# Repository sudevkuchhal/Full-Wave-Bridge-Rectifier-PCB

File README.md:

# Full Wave Bridge Rectifier PCB

## Overview
Designed and fabricated a Full Wave Bridge Rectifier PCB using KiCad.  
The circuit converts AC input into stable DC output using a diode bridge and filtering capacitor.

## Features
- Full wave AC to DC conversion
- Bridge rectifier using diodes
- Smoothing capacitor for ripple reduction
- LED power indicator

## Tools & Technologies
- KiCad (Schematic + PCB Design)
- PCB fabrication using etching method
- Soldering and hardware testing

## Learning Outcome
- PCB design workflow in KiCad
- Practical understanding of rectification
- Hands-on experience in circuit fabrication and testing
- Basics of power electronics implementation
## Project Images

### Final PCB

### Second PCB Image

### Soldering Process

### Etching Process

### Printed Layout / Setup

## Result
Successfully converted 12V AC input into stable DC output suitable for low-power electronic circuits.

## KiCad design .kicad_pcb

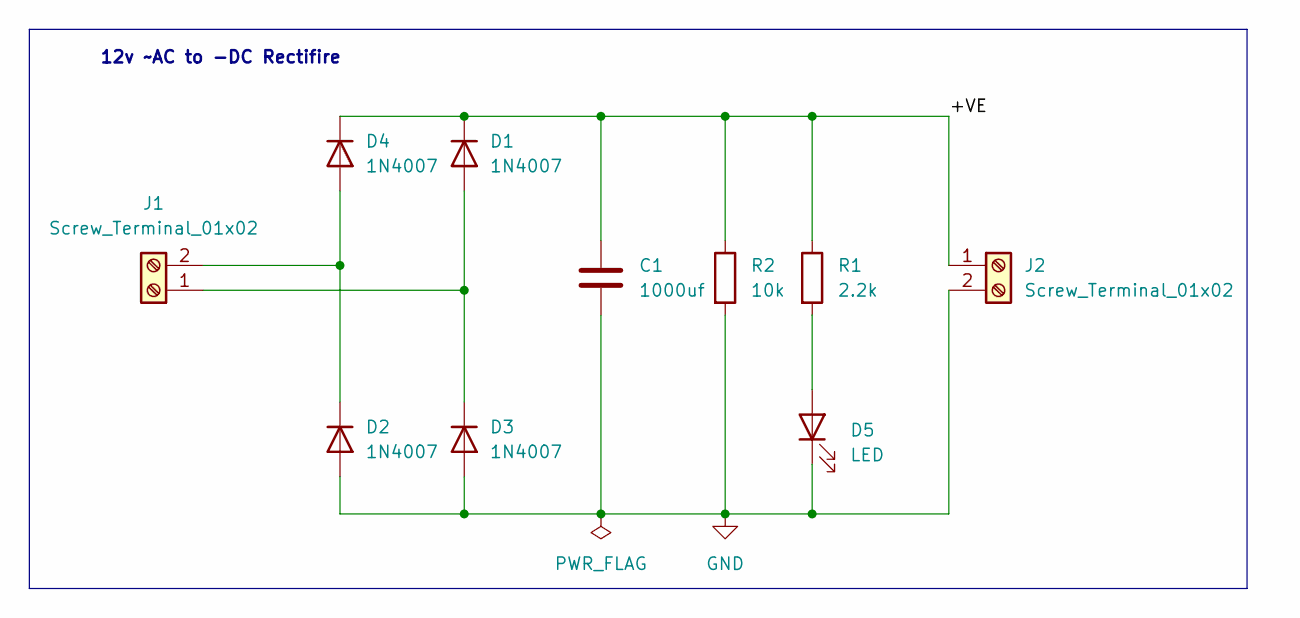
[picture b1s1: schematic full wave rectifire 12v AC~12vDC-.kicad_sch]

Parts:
C1: 1000uf; C_Radial_D8.0mm_H11.5mm_P3.50mm
D1, D2, D3, D4: 1N4007; D_DO-41_SOD81_P10.16mm_Horizontal
D5: LED; LED_D5.0mm
J1, J2: Screw_Terminal_01x02; TerminalBlock_Phoenix_MKDS-1,5-2-5.08_1x02_P5.08mm_Horizont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
R1: 2.2k; R_Axial_DIN0207_L6.3mm_D2.5mm_P7.62mm_Horizontal
R2: 10k; R_Axial_DIN0207_L6.3mm_D2.5mm_P7.62mm_Horizontal

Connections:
/+VE: C1.1, D1.1 (K), D4.1 (K), J2.1, R1.1, R2.1
GND: C1.2, D2.2 (A), D3.2 (A), D5.1 (K), J2.2, R2.2
unnamed: D1.2 (A), D3.1 (K), J1.1
unnamed: D2.1 (K), D4.2 (A), J1.2
unnamed: D5.2 (A), R1.2

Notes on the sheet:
12v ~AC to -DC Rectifire

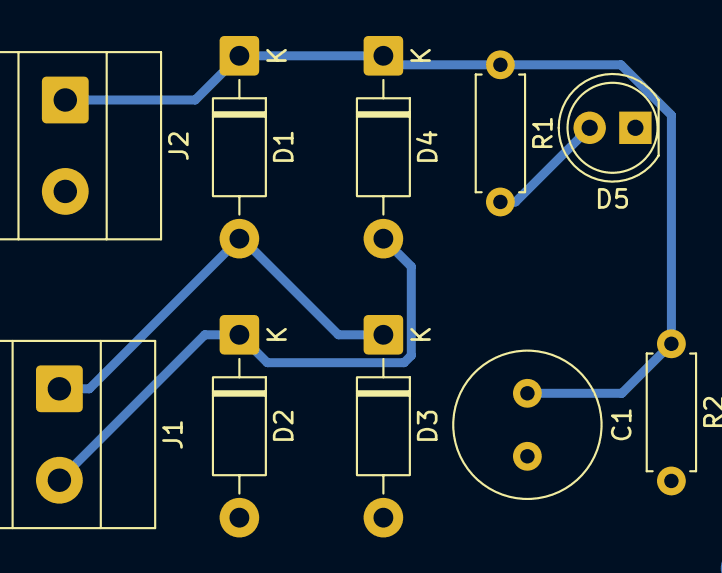
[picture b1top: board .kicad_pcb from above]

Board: 2 copper layers, 10 parts (0 on the bottom side), 5 nets.

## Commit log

2026-06-11 Initial upload: Full Wave Bridge Rectifier PCB project files
2026-06-11 Update PCB file for full wave rectifier
2026-06-11 Add .kicad_prl file for full wave rectifier project
2026-06-11 Rename project file to .kicad_pro
2026-06-11 Update .kicad_sch file for full wave rectifier
2026-06-11 Rename full wave rectifire 12v AC~12vDC-.net to .net
2026-06-11 Enhance README with project details and outcomes
    Added detailed overview, features, tools, learning outcomes, and results for the Full Wave Bridge Rectifier PCB project.
2026-06-11 Create Images
2026-06-11 Add PCB images folder
2026-06-11 Add project images and descriptions to README
    Added project images and descriptions for PCB and soldering processes.
2026-06-11 Fix image filename for printed layout in README
    Corrected image filename format for printed layout.
2026-06-11 Add section for Printed Layout / Setup
2026-06-11 Fix image filename for printed layout in README
2026-06-11 Update README to remove setup section and clarify results
    Removed 'Printed Layout / Setup' section and updated result description.
2026-06-11 Add Printed Layout / Setup section to README
    Added section for Printed Layout and Setup with image.
